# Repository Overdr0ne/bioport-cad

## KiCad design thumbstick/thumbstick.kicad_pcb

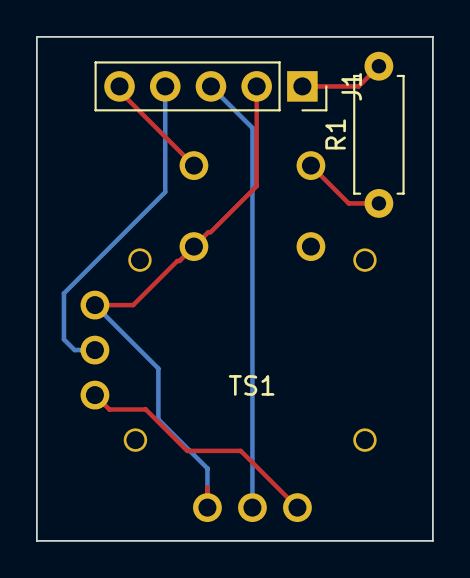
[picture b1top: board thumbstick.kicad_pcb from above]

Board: 2 copper layers, 22.0 x 28.0 mm, 3 parts (0 on the bottom side), 7 nets.

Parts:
J1: Conn_01x05_Male; PinSocket_1x05_P2.54mm_Vertical
R1: R; R_Axial_DIN0207_L6.3mm_D2.5mm_P7.62mm_Horizontal
TS1: thumbstick; joystick

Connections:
/G: TS1.XG, TS1.YG
/RG: R1.1, TS1.J2
/S: J1.5, TS1.J1
/V: J1.2, TS1.J3, TS1.XV, TS1.YV
/X: J1.3, TS1.X
/Y: J1.4, TS1.Y
unnamed: J1.1, R1.2

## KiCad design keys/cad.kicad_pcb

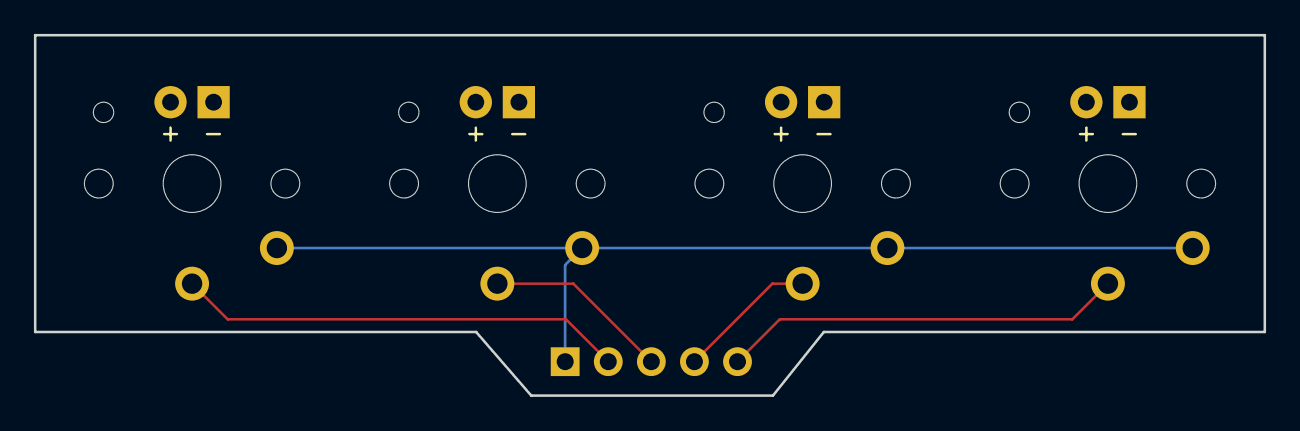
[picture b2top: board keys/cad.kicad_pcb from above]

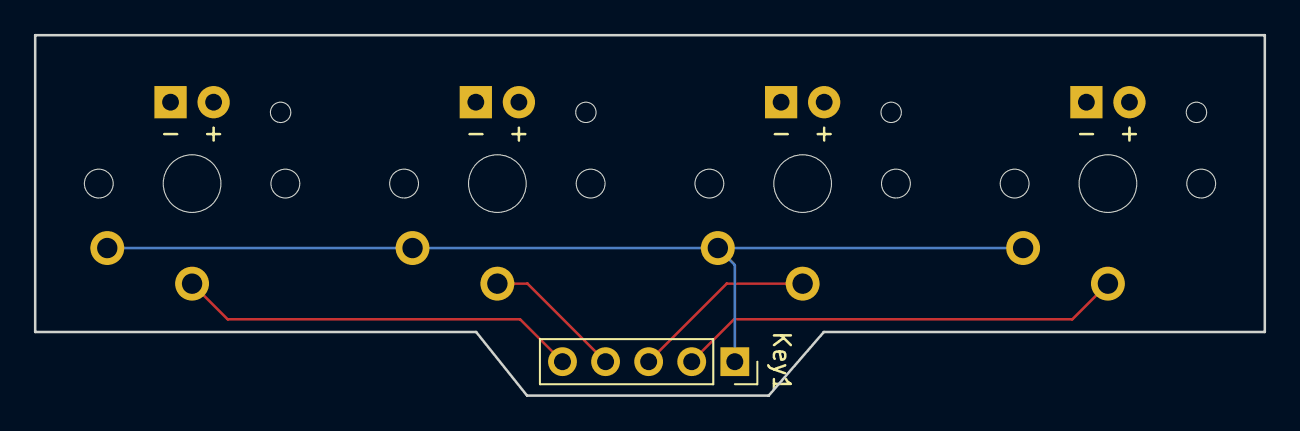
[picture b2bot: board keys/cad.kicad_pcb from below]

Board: 2 copper layers, 72.5 x 21.2 mm, 5 parts (5 on the bottom side), 5 nets.

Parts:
K?1, K?2, K?3, K?4: KEYSW; Kailh-PG1350-1u
Key1: Conn_01x05_Male; PinSocket_1x05_P2.54mm_Vertical

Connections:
unnamed: K?1.1, Key1.2
unnamed: K?1.2, K?2.2, K?3.2, K?4.2, Key1.1
unnamed: K?2.1, Key1.3
unnamed: K?3.1, Key1.4
unnamed: K?4.1, Key1.5

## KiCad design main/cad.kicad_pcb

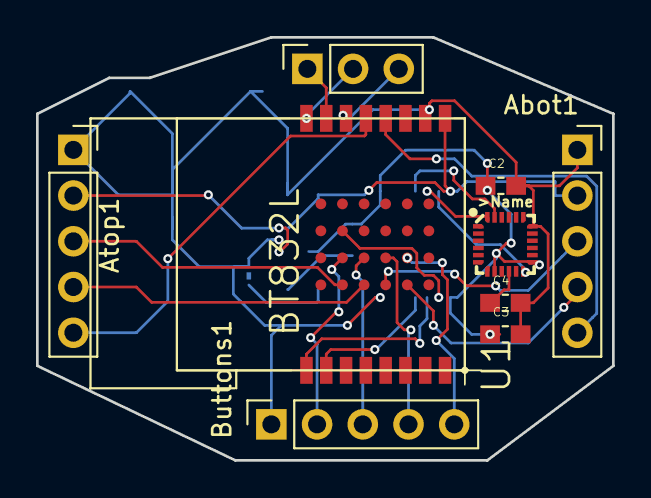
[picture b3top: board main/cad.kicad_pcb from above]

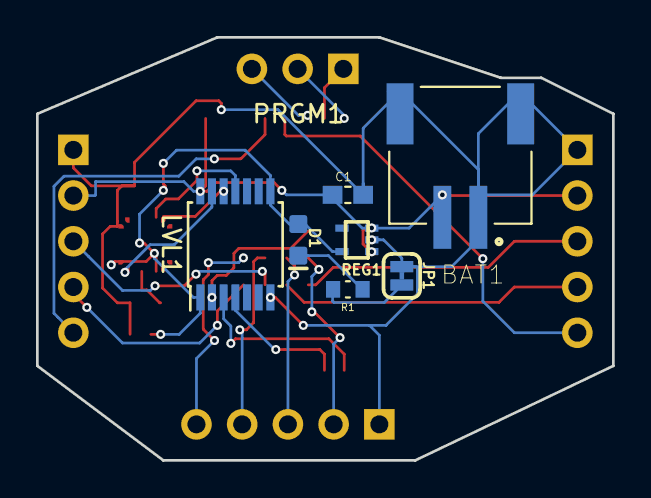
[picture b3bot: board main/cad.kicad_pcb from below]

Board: 2 copper layers, 32.0 x 23.5 mm, 16 parts (7 on the bottom side), 25 nets.

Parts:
Abot1: Conn_01x05_Male; PinSocket_1x05_P2.54mm_Vertical
Atop1: Conn_01x05_Male; PinSocket_1x05_P2.54mm_Vertical
BAT1: Conn_01x02_MountingPin; JST_S2B-PH-SM4-TB(LF)(SN)
Buttons1: Conn_01x05_Male; PinSocket_1x05_P2.54mm_Vertical
C1, C2: 1.0uF; CAPC1608X90
C3, C4: 0.1uF; CAPC1608X90
D1: RED; LED-0603
IMU1: 9DoF IMU; QFN24-3X3
JP1: LED; SMT-JUMPER_2_NC_TRACE_SILK
LVL1: TXB0104PW; TSSOP-14_4.4x5mm_P0.65mm
PRGM1: Conn_01x03_Male; PinSocket_1x03_P2.54mm_Vertical
R1: 220; RESC1608X55N
REG1: 1.8V/100mA; SC70
U1: BT832L; BT832-BT832L

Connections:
+1V8: C2.1, C3.1, D1.A, IMU1.8, IMU1.13, LVL1.1, LVL1.8, REG1.5
+3V3: Abot1.2, Atop1.2, BAT1.2, C1.1, LVL1.14, REG1.1, REG1.3, U1.P$9
/ABS: Abot1.5, U1.P$12
/ABX: Abot1.3, U1.P$A3
/ABY: Abot1.4, U1.P$A4
/ATS: Atop1.5, U1.P$13
/ATX: Atop1.3, U1.P$A1
/ATY: Atop1.4, U1.P$A2
/B1: Buttons1.2, U1.P$B1
/B2: Buttons1.3, U1.P$B2
/B3: Buttons1.4, U1.P$B3
/B4: Buttons1.5, U1.P$B4
/IMU/INT: IMU1.12, LVL1.13
/IMU/SCL_SCLK: IMU1.23, LVL1.11
/IMU/SDA_SDI: IMU1.24, LVL1.12
/INT: LVL1.2, U1.P$C1
/RESET: PRGM1.3, U1.P$14
/SCL: LVL1.4, U1.P$2
/SDA: LVL1.3, U1.P$1
/SWCLK: PRGM1.1, U1.P$15
/SWDIO: PRGM1.2, U1.P$16
GND: Abot1.1, Atop1.1, BAT1.1, BAT1.MP, Buttons1.1, C1.2, C2.2, C3.2, C4.2, IMU1.18, JP1.1, LVL1.7, REG1.2, U1.P$10
unnamed: C4.1, IMU1.10
unnamed: D1.C, R1.2
unnamed: JP1.2, R1.1

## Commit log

2021-03-05 add footprints
2021-03-05 add main pcb
2021-03-05 keys: initial commit
2021-03-05 thumbstick: initial commit
2021-03-05 main: initial commit
